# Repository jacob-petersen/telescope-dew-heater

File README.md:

# telescope-dew-heater
 4 channel dew heater controller

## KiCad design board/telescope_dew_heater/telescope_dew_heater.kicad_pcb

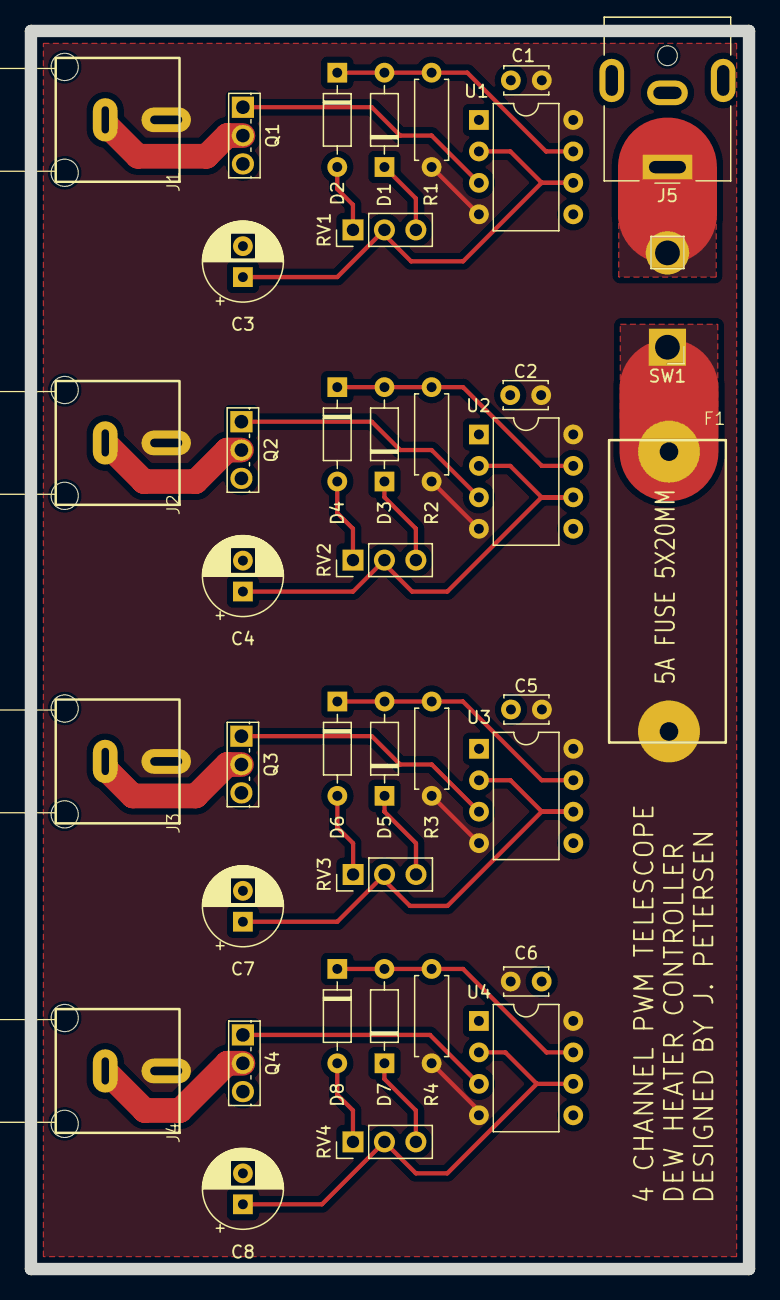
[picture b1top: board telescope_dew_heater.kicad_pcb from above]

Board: 2 copper layers, 58.0 x 100.0 mm, 39 parts (0 on the bottom side), 28 nets.

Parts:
C1, C2, C5, C6: 0.1u; C_Disc_D3.4mm_W2.1mm_P2.50mm
C3, C4, C7, C8: 68u; CP_Radial_D6.3mm_P2.50mm
D1, D2, D3, D4, D5, D6, D7, D8: D; D_DO-35_SOD27_P7.62mm_Horizontal
F1: 5A Fuse; Fuseholder_Cylinder-5x20mm_Wuerth_696108003002_THT
J1, J2, J3, J4: RCA1; KLPX-0848A-2
J5: Barrel_Jack; BarrelJack_CUI_PJ-063AH_Horizontal
Q1, Q2, Q3, Q4: Q_NMOS_GDS; TO-251-3_Vertical
R1, R2, R3, R4: 1K; R_Axial_DIN0207_L6.3mm_D2.5mm_P7.62mm_Horizontal
RV1, RV2, RV3, RV4: 100K POT; PinHeader_1x03_P2.54mm_Vertical
SW1: SW_DPDT_x2; PinHeader_1x02_P2.54mm_Vertical
U1, U2, U3, U4: NE555P; DIP-8_W7.62mm

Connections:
+12V: C1.1, C2.1, C5.1, C6.1, F1.2, J1.1 (In), J2.1 (In), J3.1 (In), J4.1 (In), R1.1, R2.1, R3.1, R4.1, U1.4 (R), U1.8 (VCC), U2.4 (R), U2.8 (VCC), U3.4 (R), U3.8 (VCC), U4.4 (R), U4.8 (VCC)
GND: C1.2, C2.2, C3.2, C4.2, C5.2, C6.2, C7.2, C8.2, J5.2, Q1.3 (S), Q2.3 (S), Q3.3 (S), Q4.3 (S), U1.1 (GND), U2.1 (GND), U3.1 (GND), U4.1 (GND)
unnamed: D1.2 (A), D2.1 (K), R1.2, U1.7 (DIS)
unnamed: D1.1 (K), RV1.3
unnamed: D2.2 (A), RV1.1
unnamed: D3.2 (A), D4.1 (K), R2.2, U2.7 (DIS)
unnamed: D3.1 (K), RV2.3
unnamed: D4.2 (A), RV2.1
unnamed: D5.2 (A), D6.1 (K), R3.2, U3.7 (DIS)
unnamed: D5.1 (K), RV3.3
unnamed: D6.2 (A), RV3.1
unnamed: D7.2 (A), D8.1 (K), R4.2, U4.7 (DIS)
unnamed: D7.1 (K), RV4.3
unnamed: D8.2 (A), RV4.1
unnamed: J1.2 (Ext), Q1.2 (D)
unnamed: J2.2 (Ext), Q2.2 (D)
unnamed: J3.2 (Ext), Q3.2 (D)
unnamed: J4.2 (Ext), Q4.2 (D)
unnamed: Q1.1 (G), U1.3 (Q)
unnamed: Q2.1 (G), U2.3 (Q)
unnamed: Q3.1 (G), U3.3 (Q)
unnamed: Q4.1 (G), U4.3 (Q)
unnamed: F1.1, SW1.1 (A)
unnamed: J5.1, SW1.2 (B)
unnamed: C3.1, RV1.2, U1.2 (TR), U1.6 (THR)
unnamed: C4.1, RV2.2, U2.2 (TR), U2.6 (THR)
unnamed: C7.1, RV3.2, U3.2 (TR), U3.6 (THR)
unnamed: C8.1, RV4.2, U4.2 (TR), U4.6 (THR)

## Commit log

2023-09-23 Started 555 circuit
2023-09-23 Updated some footprints
2023-09-25 Updated 555 circuit
    Changed cap value and type
    Added switch (still need power connector)
    Gave (almost) everything footprints (still need to give pot a connector footprint)
2023-09-25 Added falstad 555 circuit simulation file
2024-06-15 Finished PWM controller schematic, started PCB layout
    Todo: add power connector
2024-07-26 Push update
2024-08-23 4 channel version
    4 channel version of design. Committing in case I need to roll back
2024-08-23 Production Commit
    AS SUBMITTED TO PCBWAY
2024-08-27 Updated BOM
